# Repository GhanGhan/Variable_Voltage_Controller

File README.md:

# Overview
Desktop device that outputs a variable voltage whos value is controlled by the user.  The user will be able to monitor the input and output voltage and current.  This device will be suitable for prototyping, lab-bench testing and recreational purposes.
**The firmware for this projected is in the "Program" folder.**

## Notable Features!!!!!!
- Reverse voltage protection
- Power multiplexing between the input voltage terminal block and input voltage jack (explanation of circuit in section Schematic->Power->System Power Input)
  - **Allows user to hot-swap power sources while minimzing conduction losses!!!!**
- Real time voltage and current updates

## PCB Notes
- 6-Layer stackup: Signal/GNDD/VCC/PGND/AGND/Signal
- Manufactured by JLCPCB

# System Architecture
The system provides:
- A jack and terminal block for connecting to an external power supply with a range of 3-17V
- A screen to display the input voltage, input current, output voltage and output current in real time
- The ability to change the output voltage from 1.3V to 20V
- Terminal block connectors that allow an external load to connect to this device

## System Description
An external power supply connects to the device via the input connectors.  The voltage is stepped down to 3.3V to power the display, microcontroller, and voltage controller.  A voltage and current sensor measures the external power supply’s voltage and current output and sends the readings to the microcontroller.  The user can operate the voltage controller to adjust the voltage sent to the output connector, which involves either a buck or boost conversion as the output voltage can range from 0 to 20V.  Another set of voltage and current sensors measures the voltage and current delivered to the load and sends those readings to the microcontroller.  The microcontroller processes the signals received from the sensors and sends the processed data to the display, allowing the user to view the voltage and current supplied by the external power supply as well as the voltage and current delivered to the load.

# Schematics
## Power 

### System Power Input
- Power source connects to the device via a jack or a screw terminal block
- Systems needs at least 3V, and input voltage should not exceed 17V
-	Power Multiplexer circuit acts like an OR-GATE, automatically allows the higher input voltage to power the device
-	For more information about the circuit operation: [Basics of Ideal Diodes](https://www.ti.com/lit/an/slvae51a/slvae51a.pdf?ts=1756570557169&ref_url=https%253A%252F%252Fwww.google.com%252F)
-	Supplies power to the 3.3V buck converter and the buck-boost converter
### 3V3 Priority Power Multiplexing
-	Either the 3.3V buck converter or the 3.3V pin from the ST-Link programmer interface can be used to power the 3.3V circuitry
-	Priority is given to the buck converter
-	For more information about the circuit operation: [Basics of Power MUX](https://www.ti.com/lit/an/slvae51a/slvae51a.pdf?ts=1756570557169&ref_url=https%253A%252F%252Fwww.google.com%252F)
### Variable Power Output
-	Can deliver between 1.32V to 20V and up to 4A current
-	Maximum output power for each voltage given by: $P_O = \frac{5}{3}V_I + 10$
-	Potentiometer in the feedback circuitry allows the user to control the output voltage
### 3V LDO - Display Power
-	LDO used to power the LCD screen, as the nominal input voltage is 3V
### Power-On Indicator
- Indicates whether the system is receiving power

## Microcontroller

-	Powered by 3.3V and uses a 16MHz clock
-	Can be programmed/debugged via the SWD interface
- Senses the input current and voltage as well as the output current and voltage via the ADC pins
- Communicates with the LCD display via the SPI interface

## Sensors

### Current Sensors
- Composed of an 11 mΩ current-shunt resistor (shown in **Power Schematic**) and a difference amplifier with a 50V/V gain
- Senses uni-directional current up to 4A, scales output to 3.3V 
### Voltage Sensors
- Made using a voltage divider circuit
- Appropriately scaled so that the max voltage it experiences will output to 3.3V approximately

## Display

-	Powered by 3.0V
-	Has a backlight that is always on
-	Receives information about the system from the microcontroller via SPI 
- Display has a refresh rate of 10Hz

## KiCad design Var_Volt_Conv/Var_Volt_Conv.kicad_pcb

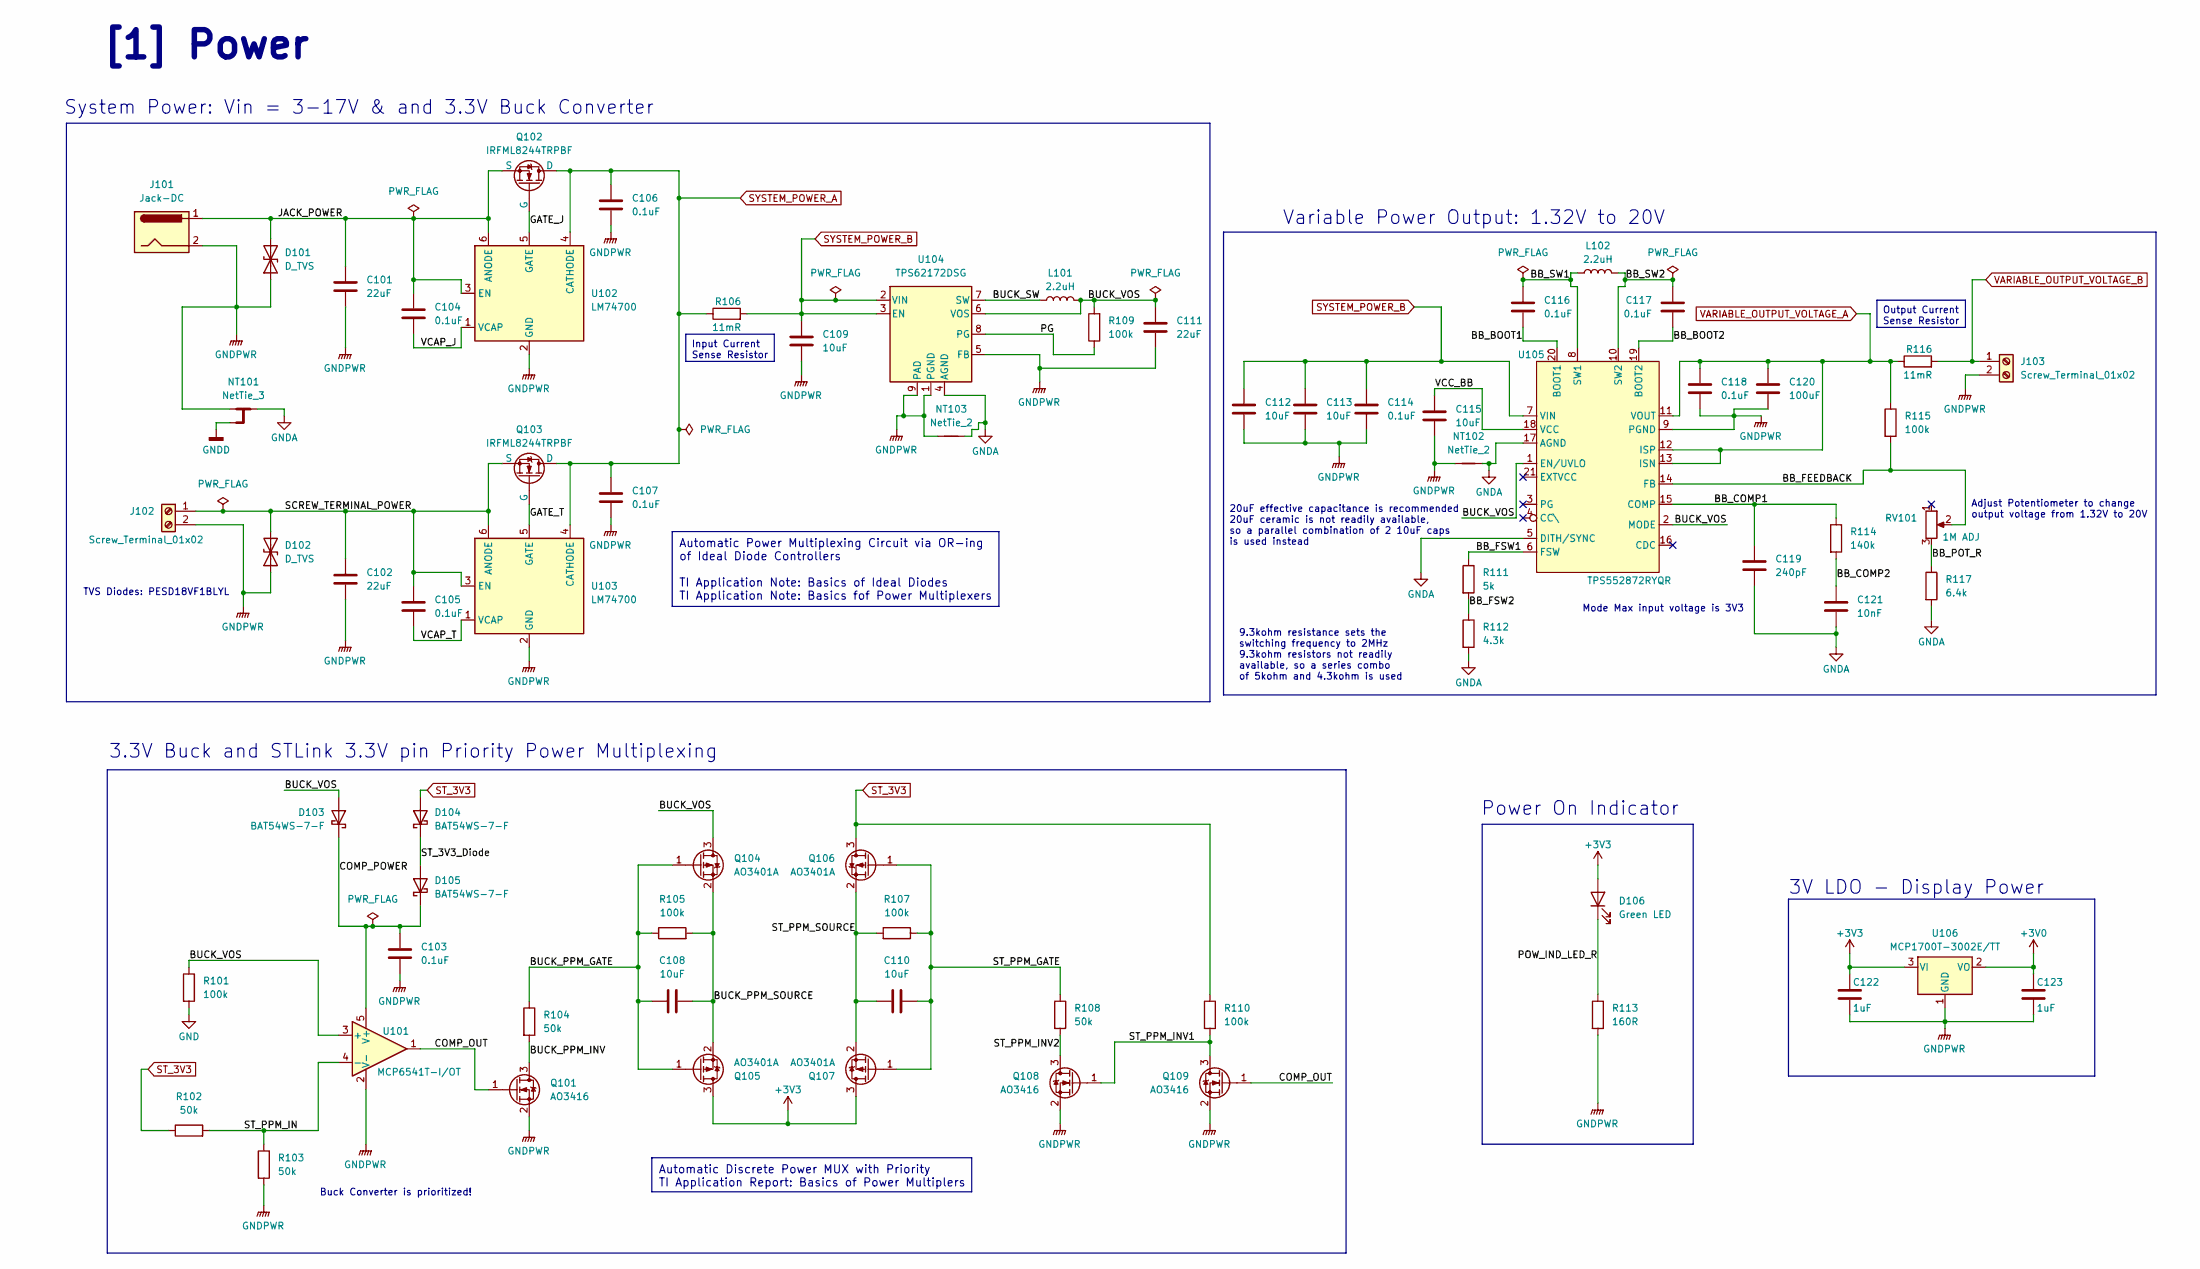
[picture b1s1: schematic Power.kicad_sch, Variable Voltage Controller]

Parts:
C101, C102, C111: 22uF; C_1206_3216Metric; Manufacturer Part # CL31A226KAHNNNE; lcsc C12891
C103, C104, C105, C106, C107, C114, C116, C117, C118: 0.1uF; C_0402_1005Metric; Manufacturer Part # CL05B104KA5NNNC; lcsc C155422
C108, C109, C110, C112, C113, C115: 10uF; C_0805_2012Metric; Manufacturer Part # CL21A106KAYNNNE; lcsc C15850
C119: 240pF; C_0603_1608Metric; Manufacturer Part # GRM1885C1H241JA01D; lcsc C185593
C120: 100uF; CP_Elec_6.3x7.7; Manufacturer Part # EEEFTH101XAP; lcsc C165974
C121: 10nF; C_0402_1005Metric; Manufacturer Part # CL05B103KB5NNNC; lcsc C15195
C122, C123: 1uF; C_0402_1005Metric; Manufacturer Part # CL05A105KA5NQNC; lcsc C52923
D101, D102: D_TVS; D_SOD-882; Manufacturer Part # PESD18VF1BLYL; lcsc C686660
D103, D104, D105: BAT54WS-7-F; D_SOD-323F; Manufacturer Part # BAT54WS-7-F; lcsc C124205
D106: Green LED; LED_0603_1608Metric; Manufacturer Part # 150060GS75000; lcsc C5252984
J101: Jack-DC; BarrelJack_CUI_PJ-063AH_Horizontal; Manufacturer Part # PJ-063AH; lcsc C2928097
J102, J103: Screw_Terminal_01x02; TerminalBlock_Phoenix_MKDS-1,5-2_1x02_P5.00mm_Horizontal; Manufacturer Part # 1984617
L101, L102: 2.2uH; L_Sunlord_MWSA0503S; Manufacturer Part # MWSA0503S-2R2MT; lcsc C408408
NT101: NetTie_3; NetTie-3_THT_Pad1.0mm
NT102, NT103: NetTie_2; NetTie-2_SMD_Pad0.5mm
Q101, Q108, Q109: AO3416; SOT-23; Manufacturer Part # AO3416; lcsc C479060
Q102, Q103: IRFML8244TRPBF; SOT-23; Manufacturer Part # IRFML8244TRPBF; lcsc C143945
Q104, Q105, Q106, Q107: AO3401A; SOT-23; Manufacturer Part # AO3401A; lcsc C15127
R101, R105, R107, R109, R110, R115: 100k; R_0402_1005Metric; Manufacturer Part # 0402WGF1003TCE; lcsc C25741
R102, R103, R104, R108: 50k; R_0402_1005Metric; Manufacturer Part # RTT025002FTH; lcsc C166559
R106, R116: 11mR; R_1210_3225Metric; Manufacturer Part # 1210W2F110MT5E; lcsc C422423
R111: 5k; R_0603_1608Metric; Manufacturer Part # RT0603BRE075KL; lcsc C862232
R112: 4.3k; R_0805_2012Metric; Manufacturer Part # 0805W8F4301T5E; lcsc C17667
R113: 160R; R_0603_1608Metric; Manufacturer Part # ERJ2RKF1600X; lcsc C413068
R114: 140k; R_0603_1608Metric; Manufacturer Part # RC0603FR-07140KL; lcsc C185372
R117: 6.4k; R_0603_1608Metric; Manufacturer Part # ARG03DTC6401N; lcsc C3014413
RV101: 1M ADJ; Potentiometer_Bourns_PTV09A-1_Single_Vertical; Manufacturer Part # PTV09A-4025F-A105
U101: MCP6541T-I/OT; SOT-353_SC-70-5; Manufacturer Part # MCP6541T-I/OT; lcsc C80839
U102, U103: LM74700; SOT-23-6; Manufacturer Part # LM74700QDBVRQ1; lcsc C2941042
U104: TPS62172DSG; WSON-8-1EP_2x2mm_P0.5mm_EP0.9x1.6mm_ThermalVias; Manufacturer Part # TPS62172DSGR; lcsc C59873
U105: TPS552872RYQR; 21-PowerVFQFN; Manufacturer Part # TPS552872RYQR; lcsc C22427496
U106: MCP1700T-3002E/TT; SOT-23; Manufacturer Part # MCP1700T-3002E/TT; lcsc C62244

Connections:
+3V0: C123.1, U106.2 (VO); also elsewhere on the board
+3V3: C122.1, D106.2 (A), Q105.3 (D), Q107.3 (D), U106.3 (VI); also elsewhere on the board
/[1] Power/BB_BOOT1: C116.2, U105.20 (BOOT1)
/[1] Power/BB_BOOT2: C117.2, U105.19 (BOOT2)
/[1] Power/BB_COMP1: C119.1, R114.1, U105.15 (COMP)
/[1] Power/BB_COMP2: C121.1, R114.2
/[1] Power/BB_FEEDBACK: R115.2, RV101.2, U105.14 (FB)
/[1] Power/BB_FSW1: R111.1, U105.6 (FSW)
/[1] Power/BB_FSW2: R111.2, R112.1
/[1] Power/BB_POT_R: R117.1, RV101.3
/[1] Power/BB_SW1: C116.1, L102.1, U105.8 (SW1)
/[1] Power/BB_SW2: C117.1, L102.2, U105.10 (SW2)
/[1] Power/BUCK_PPM_GATE: C108.1, Q104.1 (G), Q105.1 (G), R104.1, R105.1
/[1] Power/BUCK_PPM_INV: Q101.3 (D), R104.2
/[1] Power/BUCK_PPM_SOURCE: C108.2, Q104.2 (S), Q105.2 (S), R105.2
/[1] Power/BUCK_SW: L101.1, U104.7 (SW)
/[1] Power/BUCK_VOS: C111.1, D103.2 (A), L101.2, Q104.3 (D), R101.1, R109.2, U101.3 (+), U104.6 (VOS), U105.1 (EN/UVLO), U105.2 (MODE)
/[1] Power/COMP_OUT: Q101.1 (G), Q109.1 (G), U101.1
/[1] Power/COMP_POWER: C103.1, D103.1 (K), D105.1 (K), U101.5 (V+)
/[1] Power/GATE_J: Q102.1 (G), U102.5 (GATE)
/[1] Power/GATE_T: Q103.1 (G), U103.5 (GATE)
/[1] Power/JACK_POWER: C101.1, C104.1, D101.2 (A2), J101.1, Q102.2 (S), U102.3 (EN), U102.6 (ANODE)
/[1] Power/PG: R109.1, U104.8 (PG)
/[1] Power/POW_IND_LED_R: D106.1 (K), R113.1
/[1] Power/SCREW_TERMINAL_POWER: C102.1, C105.1, D102.2 (A2), J102.1, Q103.2 (S), U103.3 (EN), U103.6 (ANODE)
/[1] Power/ST_3V3_Diode: D104.1 (K), D105.2 (A)
/[1] Power/ST_PPM_GATE: C110.1, Q106.1 (G), Q107.1 (G), R107.1, R108.1
/[1] Power/ST_PPM_IN: R102.2, R103.1, U101.4 (-)
/[1] Power/ST_PPM_INV1: Q108.1 (G), Q109.3 (D), R110.2
/[1] Power/ST_PPM_INV2: Q108.3 (D), R108.2
/[1] Power/ST_PPM_SOURCE: C110.2, Q106.2 (S), Q107.2 (S), R107.2
/[1] Power/VCAP_J: C104.2, U102.1 (VCAP)
/[1] Power/VCAP_T: C105.2, U103.1 (VCAP)
/[1] Power/VCC_BB: C115.1, U105.18 (VCC)
GND: R101.2
GNDA: C119.2, C121.2, NT101.2, NT102.2, NT103.2, R112.2, R117.2, U104.4 (AGND), U105.5 (DITH/SYNC), U105.17 (AGND); also elsewhere on the board
GNDD: NT101.3; also elsewhere on the board
GNDPWR: C101.2, C102.2, C103.2, C106.2, C107.2, C109.2, C111.2, C112.2, C113.2, C114.2, C115.2, C118.2, C120.2, C122.2, C123.2, D101.1 (A1), D102.1 (A1), J101.2, J102.2, J103.2, NT101.1, NT102.1, NT103.1, Q101.2 (S), Q108.2 (S), Q109.2 (S), R103.2, R113.2, U101.2 (V-), U102.2 (GND), U103.2 (GND), U104.1 (PGND), U104.5 (FB), U104.9 (PAD), U105.9 (PGND), U106.1 (GND); also elsewhere on the board
ST_3V3: D104.2 (A), Q106.3 (D), R102.1, R110.1; also elsewhere on the board
SYSTEM_POWER_A: C106.1, C107.1, Q102.3 (D), Q103.3 (D), R106.1, U102.4 (CATHODE), U103.4 (CATHODE); also elsewhere on the board
SYSTEM_POWER_B: C109.1, C112.1, C113.1, C114.1, R106.2, U104.2 (VIN), U104.3 (EN), U105.7 (VIN); also elsewhere on the board
VARIABLE_OUTPUT_VOLTAGE_A: C118.1, C120.1, R115.1, R116.1, U105.11 (VOUT), U105.12 (ISP), U105.13 (ISN); also elsewhere on the board
VARIABLE_OUTPUT_VOLTAGE_B: J103.1, R116.2; also elsewhere on the board

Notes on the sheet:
Automatic Discrete Power MUX with Priority TI Application Report: Basics of Power Multiplers
Input Current Sense Resistor
Output Current Sense Resistor
Automatic Power Multiplexing Circuit via OR-ing of Ideal Diode Controllers TI Application Note: Basics of Ideal Diodes TI Application Note: Basics fof Power Multiplexers
9.3kohm resistance sets the switching frequency to 2MHz 9.3kohm resistors not readily available, so a series combo of 5kohm and 4.3kohm is used
System Power: Vin = 3-17V & and 3.3V Buck Converter
Variable Power Output: 1.32V to 20V
TVS Diodes: PESD18VF1BLYL
3V LDO - Display Power
Buck Converter is prioritized!
Mode Max input voltage is 3V3
[1] Power
Power On Indicator
20uF effective capacitance is recommended 20uF ceramic is not readily available, so a parallel combination of 2 10uF caps is used instead
Adjust Potentiometer to change output voltage from 1.32V to 20V
3.3V Buck and STLink 3.3V pin Priority Power Multiplexing

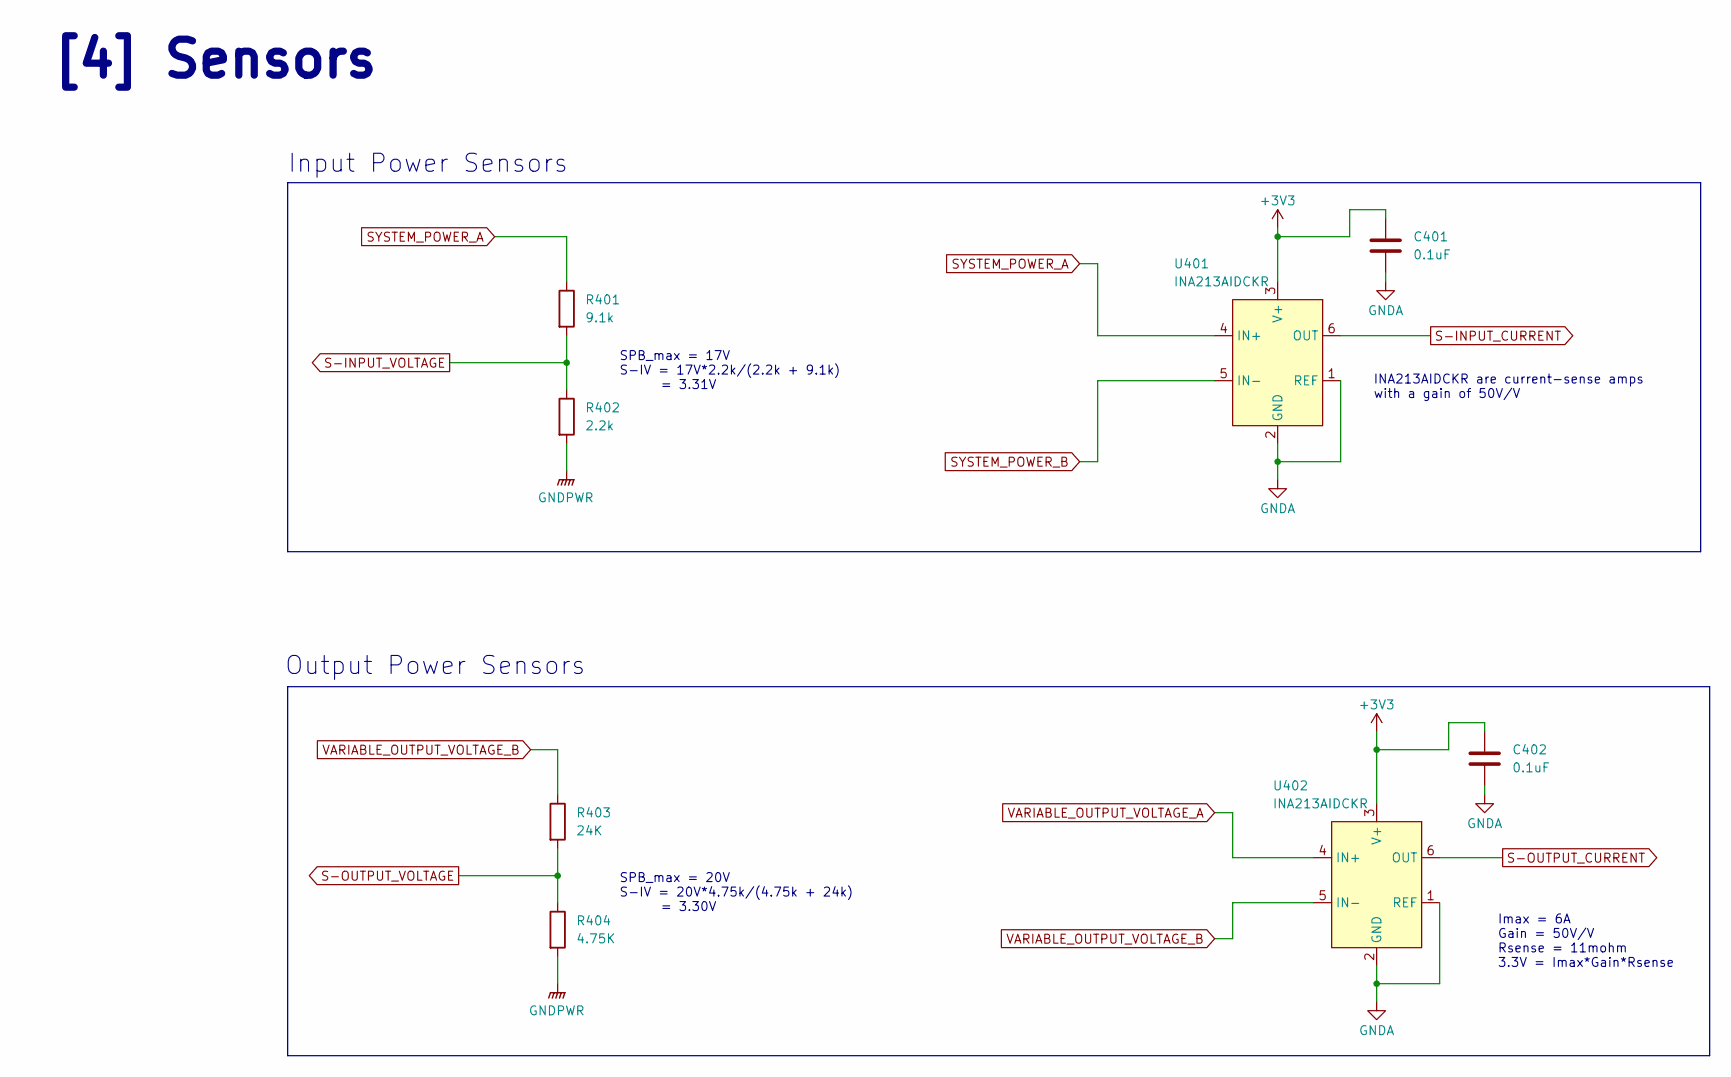
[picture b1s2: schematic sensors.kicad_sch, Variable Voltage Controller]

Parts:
C401, C402: 0.1uF; C_0402_1005Metric; Manufacturer Part # CL05B104KA5NNNC; lcsc C155422
R401: 9.1k; R_0603_1608Metric; Manufacturer Part # 0603WAF9101T5E; lcsc C23260
R402: 2.2k; R_0603_1608Metric; Manufacturer Part # 0603WAF2201T5E; lcsc C4190
R403: 24K; R_0402_1005Metric; Manufacturer Part # ERJ2RKF2402X; lcsc C409902
R404: 4.75K; R_0402_1005Metric; Manufacturer Part # 0402WGF4751TCE; lcsc C25901
U401, U402: INA213AIDCKR; SOT-363_SC-70-6; Manufacturer Part # INA213AIDCKR; lcsc C129346

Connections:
+3V3: C401.1, C402.1, U401.3 (V+), U402.3 (V+); also elsewhere on the board
GNDA: C401.2, C402.2, U401.1 (REF), U401.2 (GND), U402.1 (REF), U402.2 (GND); also elsewhere on the board
GNDPWR: R402.2, R404.2; also elsewhere on the board
S-INPUT_CURRENT: U401.6 (OUT); also elsewhere on the board
S-INPUT_VOLTAGE: R401.2, R402.1; also elsewhere on the board
S-OUTPUT_CURRENT: U402.6 (OUT); also elsewhere on the board
S-OUTPUT_VOLTAGE: R403.2, R404.1; also elsewhere on the board
SYSTEM_POWER_A: R401.1, U401.4 (IN+); also elsewhere on the board
SYSTEM_POWER_B: U401.5 (IN-); also elsewhere on the board
VARIABLE_OUTPUT_VOLTAGE_A: U402.4 (IN+); also elsewhere on the board
VARIABLE_OUTPUT_VOLTAGE_B: R403.1, U402.5 (IN-); also elsewhere on the board

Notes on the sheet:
INA213AIDCKR are current-sense amps with a gain of 50V/V
Output Power Sensors
Imax = 6A Gain = 50V/V Rsense = 11mohm 3.3V = Imax*Gain*Rsense
SPB_max = 17V S-IV = 17V*2.2k/(2.2k + 9.1k) = 3.31V
[4] Sensors
Input Power Sensors
SPB_max = 20V S-IV = 20V*4.75k/(4.75k + 24k) = 3.30V

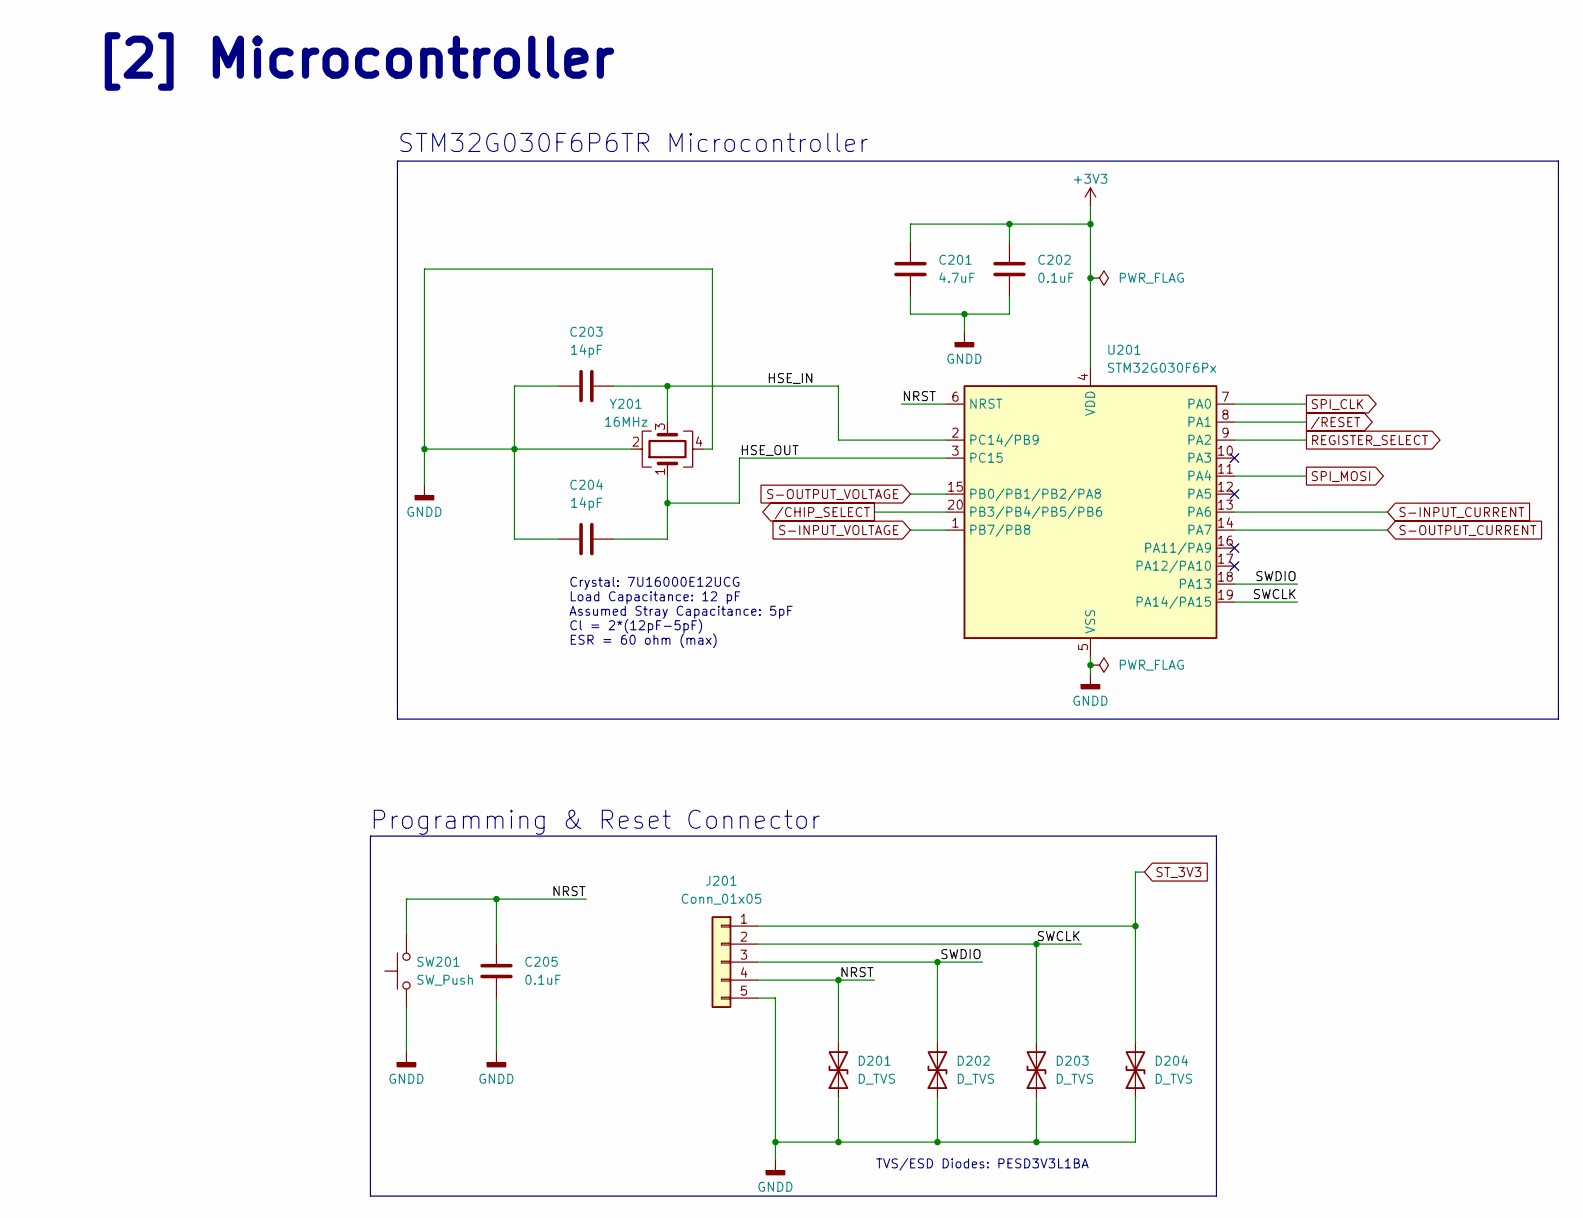
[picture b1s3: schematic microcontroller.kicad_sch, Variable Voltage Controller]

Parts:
C201: 4.7uF; C_0402_1005Metric; Manufacturer Part # CL05A475MP5NRNC; lcsc C23733
C202, C205: 0.1uF; C_0402_1005Metric; Manufacturer Part # CL05B104KA5NNNC; lcsc C155422
C203, C204: 14pF; C_0402_1005Metric; Manufacturer Part # 0402N140J500CT; lcsc C458857
D201, D202, D203, D204: D_TVS; D_SOD-323; Manufacturer Part # PESD3V3L1BA,115; lcsc C51450
J201: Conn_01x05; PinHeader_1x05_P2.54mm_Vertical; Manufacturer Part # PPTC051LFBN-RC
SW201: SW_Push; SW_Tactile_SPST_NO_Straight_CK_PTS636Sx25SMTRLFS; Manufacturer Part # PTS636SKG25SMTR LFS
U201: STM32G030F6Px; TSSOP-20_4.4x6.5mm_P0.65mm; Manufacturer Part # STM32G030F6P6; lcsc C724040
Y201: 16MHz; Crystal_SMD_3225-4Pin_3.2x2.5mm; Manufacturer Part # 7U16000E12UCG; lcsc C251610

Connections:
+3V3: C201.1, C202.1, U201.4 (VDD); also elsewhere on the board
/[2] Microcontroller/HSE_IN: C203.2, U201.2 (PC14/PB9), Y201.3
/[2] Microcontroller/HSE_OUT: C204.2, U201.3 (PC15), Y201.1
/[2] Microcontroller/NRST: C205.1, D201.2 (A2), J201.4, SW201.2, U201.6 (NRST)
/[2] Microcontroller/SWCLK: D203.2 (A2), J201.2, U201.19 (PA14/PA15)
/[2] Microcontroller/SWDIO: D202.2 (A2), J201.3, U201.18 (PA13)
GNDD: C201.2, C202.2, C203.1, C204.1, C205.2, D201.1 (A1), D202.1 (A1), D203.1 (A1), D204.1 (A1), J201.5, SW201.1, U201.5 (VSS), Y201.2, Y201.4; also elsewhere on the board
REGISTER_SELECT: U201.9 (PA2); also elsewhere on the board
S-INPUT_CURRENT: U201.13 (PA6); also elsewhere on the board
S-INPUT_VOLTAGE: U201.1 (PB7/PB8); also elsewhere on the board
S-OUTPUT_CURRENT: U201.14 (PA7); also elsewhere on the board
S-OUTPUT_VOLTAGE: U201.15 (PB0/PB1/PB2/PA8); also elsewhere on the board
SPI_CLK: U201.7 (PA0); also elsewhere on the board
SPI_MOSI: U201.11 (PA4); also elsewhere on the board
ST_3V3: D204.2 (A2), J201.1; also elsewhere on the board
/CHIP_SELECT: U201.20 (PB3/PB4/PB5/PB6); also elsewhere on the board
/RESET: U201.8 (PA1); also elsewhere on the board

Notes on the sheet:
TVS/ESD Diodes: PESD3V3L1BA
Programming & Reset Connector
Crystal: 7U16000E12UCG Load Capacitance: 12 pF Assumed Stray Capacitance: 5pF Cl = 2*(12pF-5pF) ESR = 60 ohm (max)
STM32G030F6P6TR Microcontroller
[2] Microcontroller

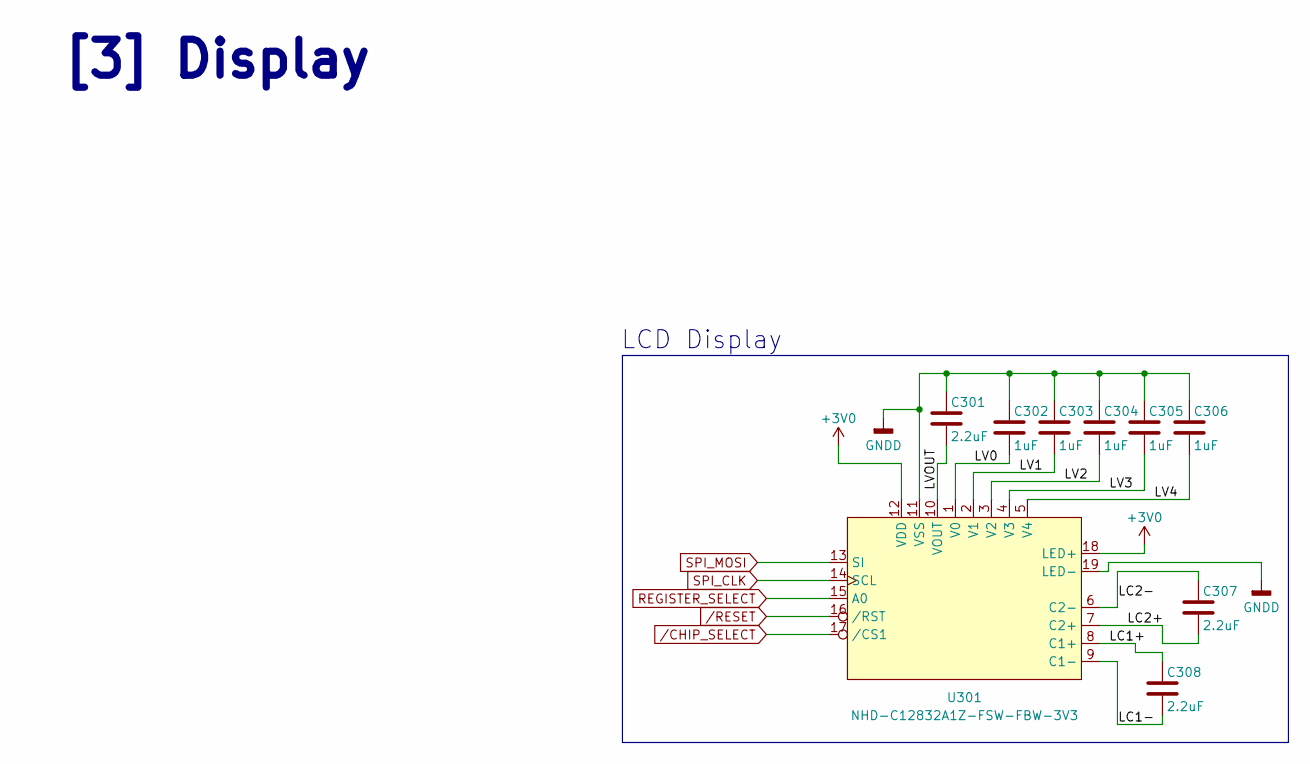
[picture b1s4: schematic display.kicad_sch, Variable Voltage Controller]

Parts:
C301, C307, C308: 2.2uF; C_0402_1005Metric; Manufacturer Part # CL05A225MQ5NSNC; lcsc C12530
C302, C303, C304, C305, C306: 1uF; C_0402_1005Metric; Manufacturer Part # CL05A105KA5NQNC; lcsc C52923
U301: NHD-C12832A1Z-FSW-FBW-3V3; NHD-C12832A1Z-FSRGB; Manufacturer Part # NHD-C12832A1Z-FSW-FBW-3V3

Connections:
+3V0: U301.12 (VDD), U301.18 (LED+); also elsewhere on the board
/[3] Display/LC1+: C308.1, U301.8 (C1+)
/[3] Display/LC1-: C308.2, U301.9 (C1-)
/[3] Display/LC2+: C307.2, U301.7 (C2+)
/[3] Display/LC2-: C307.1, U301.6 (C2-)
/[3] Display/LV0: C302.2, U301.1 (V0)
/[3] Display/LV1: C303.2, U301.2 (V1)
/[3] Display/LV2: C304.2, U301.3 (V2)
/[3] Display/LV3: C305.2, U301.4 (V3)
/[3] Display/LV4: C306.2, U301.5 (V4)
/[3] Display/LVOUT: C301.2, U301.10 (VOUT)
GNDD: C301.1, C302.1, C303.1, C304.1, C305.1, C306.1, U301.11 (VSS), U301.19 (LED-); also elsewhere on the board
REGISTER_SELECT: U301.15 (A0); also elsewhere on the board
SPI_CLK: U301.14 (SCL); also elsewhere on the board
SPI_MOSI: U301.13 (SI); also elsewhere on the board
/CHIP_SELECT: U301.17 (/CS1); also elsewhere on the board
/RESET: U301.16 (/RST); also elsewhere on the board

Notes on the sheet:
LCD Display
[3] Display

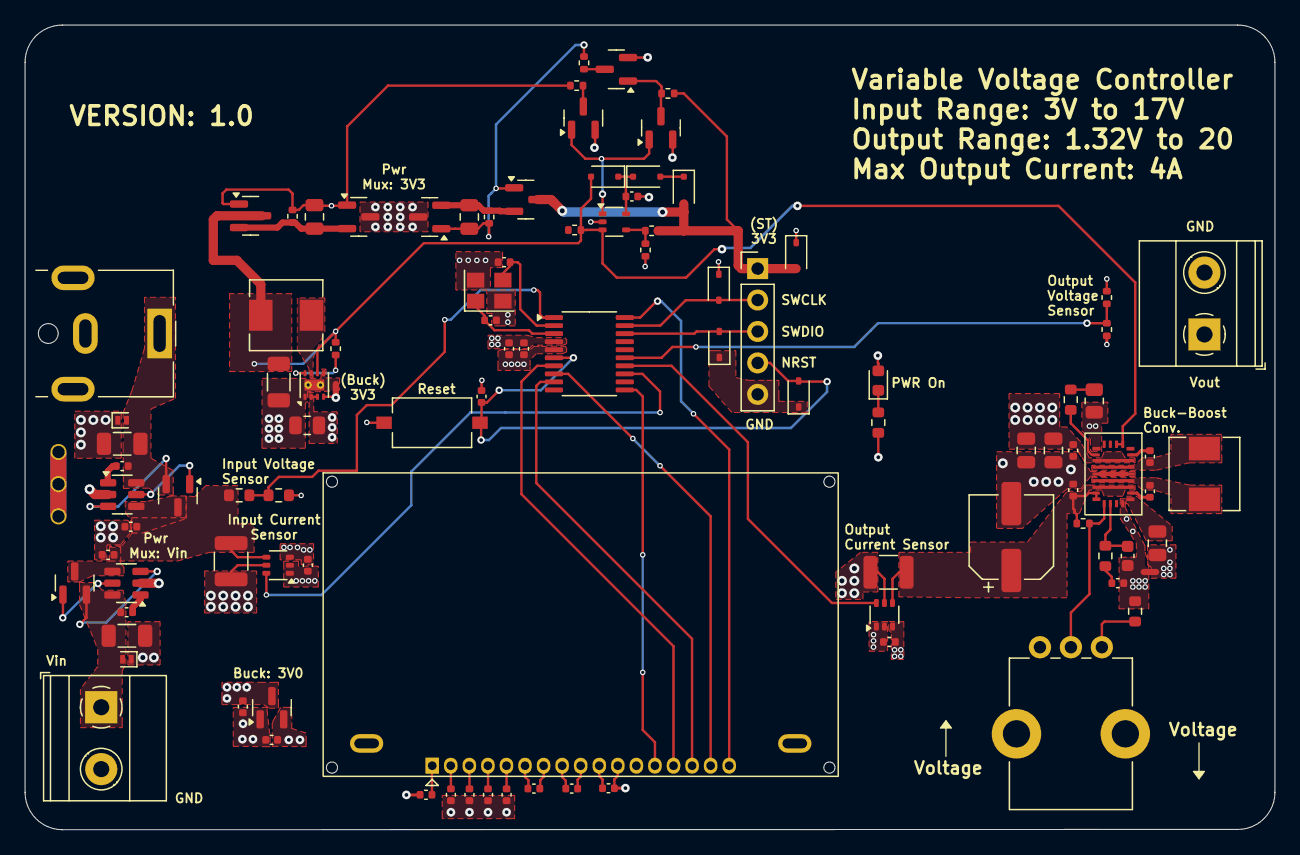
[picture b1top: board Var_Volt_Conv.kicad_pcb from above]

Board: 6 copper layers, 101.0 x 65.0 mm, 100 parts (0 on the bottom side), 66 nets.

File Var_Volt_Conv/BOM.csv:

"#","Reference","Value","Footprint","Qty","lcsc","Manufacturer Part #"
"1","C101,C102,C111","22uF","Capacitor_SMD:C_1206_3216Metric","3","C12891 ","CL31A226KAHNNNE "
"2","C103,C104,C105,C106,C107,C114,C116,C117,C118,C202,C205,C401,C402","0.1uF","Capacitor_SMD:C_0402_1005Metric","13","C155422","CL05B104KA5NNNC"
"3","C108,C109,C110,C112,C113,C115","10uF","Capacitor_SMD:C_0805_2012Metric","6","C15850 ","CL21A106KAYNNNE "
"4","C119","240pF","Capacitor_SMD:C_0603_1608Metric","1","C185593","GRM1885C1H241JA01D"
"5","C120","100uF","Capacitor_SMD:CP_Elec_6.3x7.7","1","C165974","EEEFTH101XAP"
"6","C121","10nF","Capacitor_SMD:C_0402_1005Metric","1","C15195 ","CL05B103KB5NNNC "
"7","C122,C123,C302,C303,C304,C305,C306","1uF","Capacitor_SMD:C_0402_1005Metric","7","C52923","CL05A105KA5NQNC"
"8","C201","4.7uF","Capacitor_SMD:C_0402_1005Metric","1","C23733","CL05A475MP5NRNC"
"9","C203,C204","14pF","Capacitor_SMD:C_0402_1005Metric","2","C458857","0402N140J500CT"
"10","C301,C307,C308","2.2uF","Capacitor_SMD:C_0402_1005Metric","3","C12530","CL05A225MQ5NSNC"
"11","D101,D102","D_TVS","Diode_SMD:D_SOD-882","2","C686660","PESD18VF1BLYL"
"12","D103,D104,D105","BAT54WS-7-F","Diode_SMD:D_SOD-323F","3","C124205","BAT54WS-7-F"
"13","D106","Green LED","LED_SMD:LED_0603_1608Metric","1","C5252984","150060GS75000"
"14","D201,D202,D203,D204","D_TVS","Diode_SMD:D_SOD-323","4","C51450","PESD3V3L1BA,115"
"15","J101","Jack-DC","Connector_BarrelJack:BarrelJack_CUI_PJ-063AH_Horizontal","1","C2928097","PJ-063AH"
"16","J102,J103","Screw_Terminal_01x02","TerminalBlock_Phoenix:TerminalBlock_Phoenix_MKDS-1,5-2_1x02_P5.00mm_Horizontal","2","","1984617"
"17","J201","Conn_01x05","Connector_PinHeader_2.54mm:PinHeader_1x05_P2.54mm_Vertical","1","","PPTC051LFBN-RC"
"18","L101,L102","2.2uH","Inductor_SMD:L_Sunlord_MWSA0503S","2","C408408","MWSA0503S-2R2MT"
"19","Q101,Q108,Q109,Q110","AO3416","Package_TO_SOT_SMD:SOT-23","4","C479060","AO3416"
"20","Q102,Q103","IRFML8244TRPBF","Package_TO_SOT_SMD:SOT-23","2","C143945","IRFML8244TRPBF"
"21","Q104,Q105,Q106,Q107","AO3407","Package_TO_SOT_SMD:SOT-23","4","C351408","AO3407"
"22","R101,R104,R105,R107,R108,R109,R110,R115","100k","Resistor_SMD:R_0402_1005Metric","8","C25741","0402WGF1003TCE"
"23","R102,R103","50k","Resistor_SMD:R_0402_1005Metric","2","C166559","RTT025002FTH"
"24","R106,R116","11mR","Resistor_SMD:R_1210_3225Metric","2","C422423","1210W2F110MT5E"
"25","R111","5k","Resistor_SMD:R_0603_1608Metric","1","C862232","RT0603BRE075KL"
"26","R112","4.3k","Resistor_SMD:R_0805_2012Metric","1","C17667","0805W8F4301T5E"
"27","R113","160R","Resistor_SMD:R_0603_1608Metric","1","C413068","ERJ2RKF1600X"
"28","R114","140k","Resistor_SMD:R_0603_1608Metric","1","C185372","RC0603FR-07140KL"
"29","R117","6.4k","Resistor_SMD:R_0603_1608Metric","1","C3014413","ARG03DTC6401N"
"30","R401","9.1k","Resistor_SMD:R_0603_1608Metric","1","C23260","0603WAF9101T5E"
"31","R402","2.2k","Resistor_SMD:R_0603_1608Metric","1","C4190","0603WAF2201T5E"
"32","R403","24K","Resistor_SMD:R_0402_1005Metric","1","C409902","ERJ2RKF2402X"
"33","R404","4.75K","Resistor_SMD:R_0402_1005Metric","1","C25901 ","0402WGF4751TCE"
"34","RV101","1M ADJ","Potentiometer_THT:Potentiometer_Bourns_PTV09A-1_Single_Vertical","1","","PTV09A-4025F-A105"
"35","SW201","SW_Push","Button_Switch_SMD:SW_Tactile_SPST_NO_Straight_CK_PTS636Sx25SMTRLFS","1","","PTS636SKG25SMTR LFS"
"36","U101","MCP6541T-I/OT","Package_TO_SOT_SMD:SOT-353_SC-70-5","1","C80839","MCP6541T-I/OT"
"37","U102,U103","LM74700","Package_TO_SOT_SMD:SOT-23-6","2","C2941042","LM74700QDBVRQ1"
"38","U104","TPS62172DSG","Package_SON:WSON-8-1EP_2x2mm_P0.5mm_EP0.9x1.6mm_ThermalVias","1","C59873","TPS62172DSGR"
"39","U105","TPS552872RYQR","Buck_Boost:21-PowerVFQFN","1","C22427496","TPS552872RYQR"
"40","U106","MCP1700T-3002E/TT","Package_TO_SOT_SMD:SOT-23","1","C62244","MCP1700T-3002E/TT"
"41","U201","STM32G030F6Px","Package_SO:TSSOP-20_4.4x6.5mm_P0.65mm","1","C724040","STM32G030F6P6"
"42","U301","NHD-C12832A1Z-FSW-FBW-3V3","Display:NHD-C12832A1Z-FSRGB","1","","NHD-C12832A1Z-FSW-FBW-3V3"
"43","U401,U402","INA213AIDCKR","Package_TO_SOT_SMD:SOT-363_SC-70-6","2","C129346","INA213AIDCKR"
"44","Y201","16MHz","Crystal:Crystal_SMD_3225-4Pin_3.2x2.5mm","1","C251610","7U16000E12UCG"

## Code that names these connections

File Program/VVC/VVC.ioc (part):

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Mcu.Name=STM32G030F6Px
Mcu.Package=TSSOP20
Mcu.UserName=STM32G030F6Px
PA0.Mode=Simplex_Bidirectional_Master
PA0.Signal=SPI2_SCK
PA1.GPIOParameters=GPIO_Label
PA1.GPIO_Label=_RST
PA1.Signal=GPIO_Output
PA13.Mode=Serial_Wire
PA13.Signal=SYS_SWDIO
PA14-BOOT0.Mode=Serial_Wire
PA14-BOOT0.Signal=SYS_SWCLK
PA14-BOOT0__PA15.StandardMode=true
PA2.GPIOParameters=GPIO_Label
PA2.GPIO_Label=A0
PA2.Signal=GPIO_Output
PA4.Mode=Simplex_Bidirectional_Master
PA4.Signal=SPI2_MOSI
PA6.GPIOParameters=GPIO_Label
PA6.GPIO_Label=S-Input Current
PA6.Mode=IN6
PA6.Signal=ADC1_IN6
PA7.GPIOParameters=GPIO_Label
PA7.GPIO_Label=S-Output Current
PA7.Mode=IN7
PA7.Signal=ADC1_IN7
PB0.GPIOParameters=GPIO_Label
PB0.GPIO_Label=S-Output Voltage
PB0.Mode=IN8
PB0.Signal=ADC1_IN8
PB0__PB1__PB2__PA8.StandardMode=true
PB3.GPIOParameters=GPIO_Label
PB3.GPIO_Label=_CS
PB3.Signal=GPIO_Output
PB3__PB4__PB5__PB6.StandardMode=true
PB7.GPIOParameters=GPIO_Label
PB7.GPIO_Label=S-Input Voltage
PB7.Mode=IN11
PB7.Signal=ADC1_IN11
PB7__PB8.StandardMode=true
PC14-OSC32_IN\ (PC14)__PB9.StandardMode=true
RCC.HSE_VALUE=8000000
RCC.SYSCLKFreq_VALUE=16000000
board=custom
